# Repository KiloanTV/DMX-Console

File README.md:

<div>
  <h1 align="center">DMX Console</h1>

  <p align="center">
  <a href="https://blueprint.hackclub.com/">
    </img>
  </a>
  </p>
  <h1></h1>
  <p align="center">
    Nodes to build a custom DMX Console yourself!
  </p>
</div>

<sub align="center">This work is licensed under the
[MIT License](https://mit-license.org).
</sub>

## Table of Contents

- [About](#about)
- [Pictures](#pictures)
- [Bill of Materials](#bill-of-materials)

# About

I really wanted to build my own DMX Console but with modules and nodes so everyone can make a combination which work for themself. I havent designed the display driver board and the network switch yet but that will be in the V2 in the future.

# Pictures

# Bill of Materials

<details>
<summary><strong>Show Bill Of Materials(BOM) ----></strong></summary>

|Part Name                                     |Quantity                                    |Price            |Vendor    |Shipping Cost                                                  |Total Cost      |Link(if applicable)                                                                                                                                                                                                                                                                                                                                                                                                                                                                                                                                                                                                           |FIELD8|
|----------------------------------------------|--------------------------------------------|-----------------|----------|---------------------------------------------------------------|----------------|------------------------------------------------------------------------------------------------------------------------------------------------------------------------------------------------------------------------------------------------------------------------------------------------------------------------------------------------------------------------------------------------------------------------------------------------------------------------------------------------------------------------------------------------------------------------------------------------------------------------------|------|
|All 5 different PCBs + Stencils               |1x5 of each                                 |€84.74           |jlcpcb    |Shipping for all 3 PCB orders + taxes (see screenshot): €61.76 |                |                                                                                                                                                                                                                                                                                                                                                                                                                                                                                                                                                                                                                              |      |
|LCSC Electronic Components for 1x of every PCB|1 Order for everything(see lcsc cart export)|€135.83          |lcsc      |€49,63 (there is a Tariff for EU handling fees, see screenshot)|                |                                                                                                                                                                                                                                                                                                                                                                                                                                                                                                                                                                                                                              |      |
|motorized fader                               |4x1pcs                                      |€15,52           |alibaba   |€11.21                                                         |                |https://www.alibaba.com/product-detail/Terwin-X32-Motor-Fader-100mm-Travel_1601238129471.html?spm=a2700.prosearch.normal_offer.d_image.2e8f67afmJxxMf&priceId=ad31270e432b4abc9cdc3bcf5230f13c                                                                                                                                                                                                                                                                                                                                                                                                                                |      |
|Keyswitches                                   |4x1pcs                                      |€5,42            |aliexpress|€12.59                                                         |                |https://de.aliexpress.com/item/1005009946528694.html?spm=a2g0o.productlist.main.6.577b5ba0rvdL0e&algo_pvid=3587bc3c-6277-4f81-b946-1ec385545323&algo_exp_id=3587bc3c-6277-4f81-b946-1ec385545323-5&pdp_ext_f=%7B%22order%22%3A%2226%22%2C%22eval%22%3A%221%22%2C%22fromPage%22%3A%22search%22%7D&pdp_npi=6%40dis%21EUR%211.79%211.79%21%21%211.96%211.96%21%400b88ab8a17934589390817509e0f02%2112000050653018363%21sea%21DE%210%21X%211%210%21n_tag%3A-29919%3Bd%3A579054d5%3Bm03_new_user%3A-29895&curPageLogUid=jCaWmj7inoTK&utparam-url=scene%3Asearch%7Cquery_from%3A%7Cx_object_id%3A1005009946528694%7C_p_origin_prod%3A|      |
|Estimated Total                               |                                            |€241,51 ($270,48)|          |€135,19 ($151,41)                                              |€376,7 ($421,89)|                                                                                                                                                                                                                                                                                                                                                                                                                                                                                                                                                                                                                              |      |

</details>

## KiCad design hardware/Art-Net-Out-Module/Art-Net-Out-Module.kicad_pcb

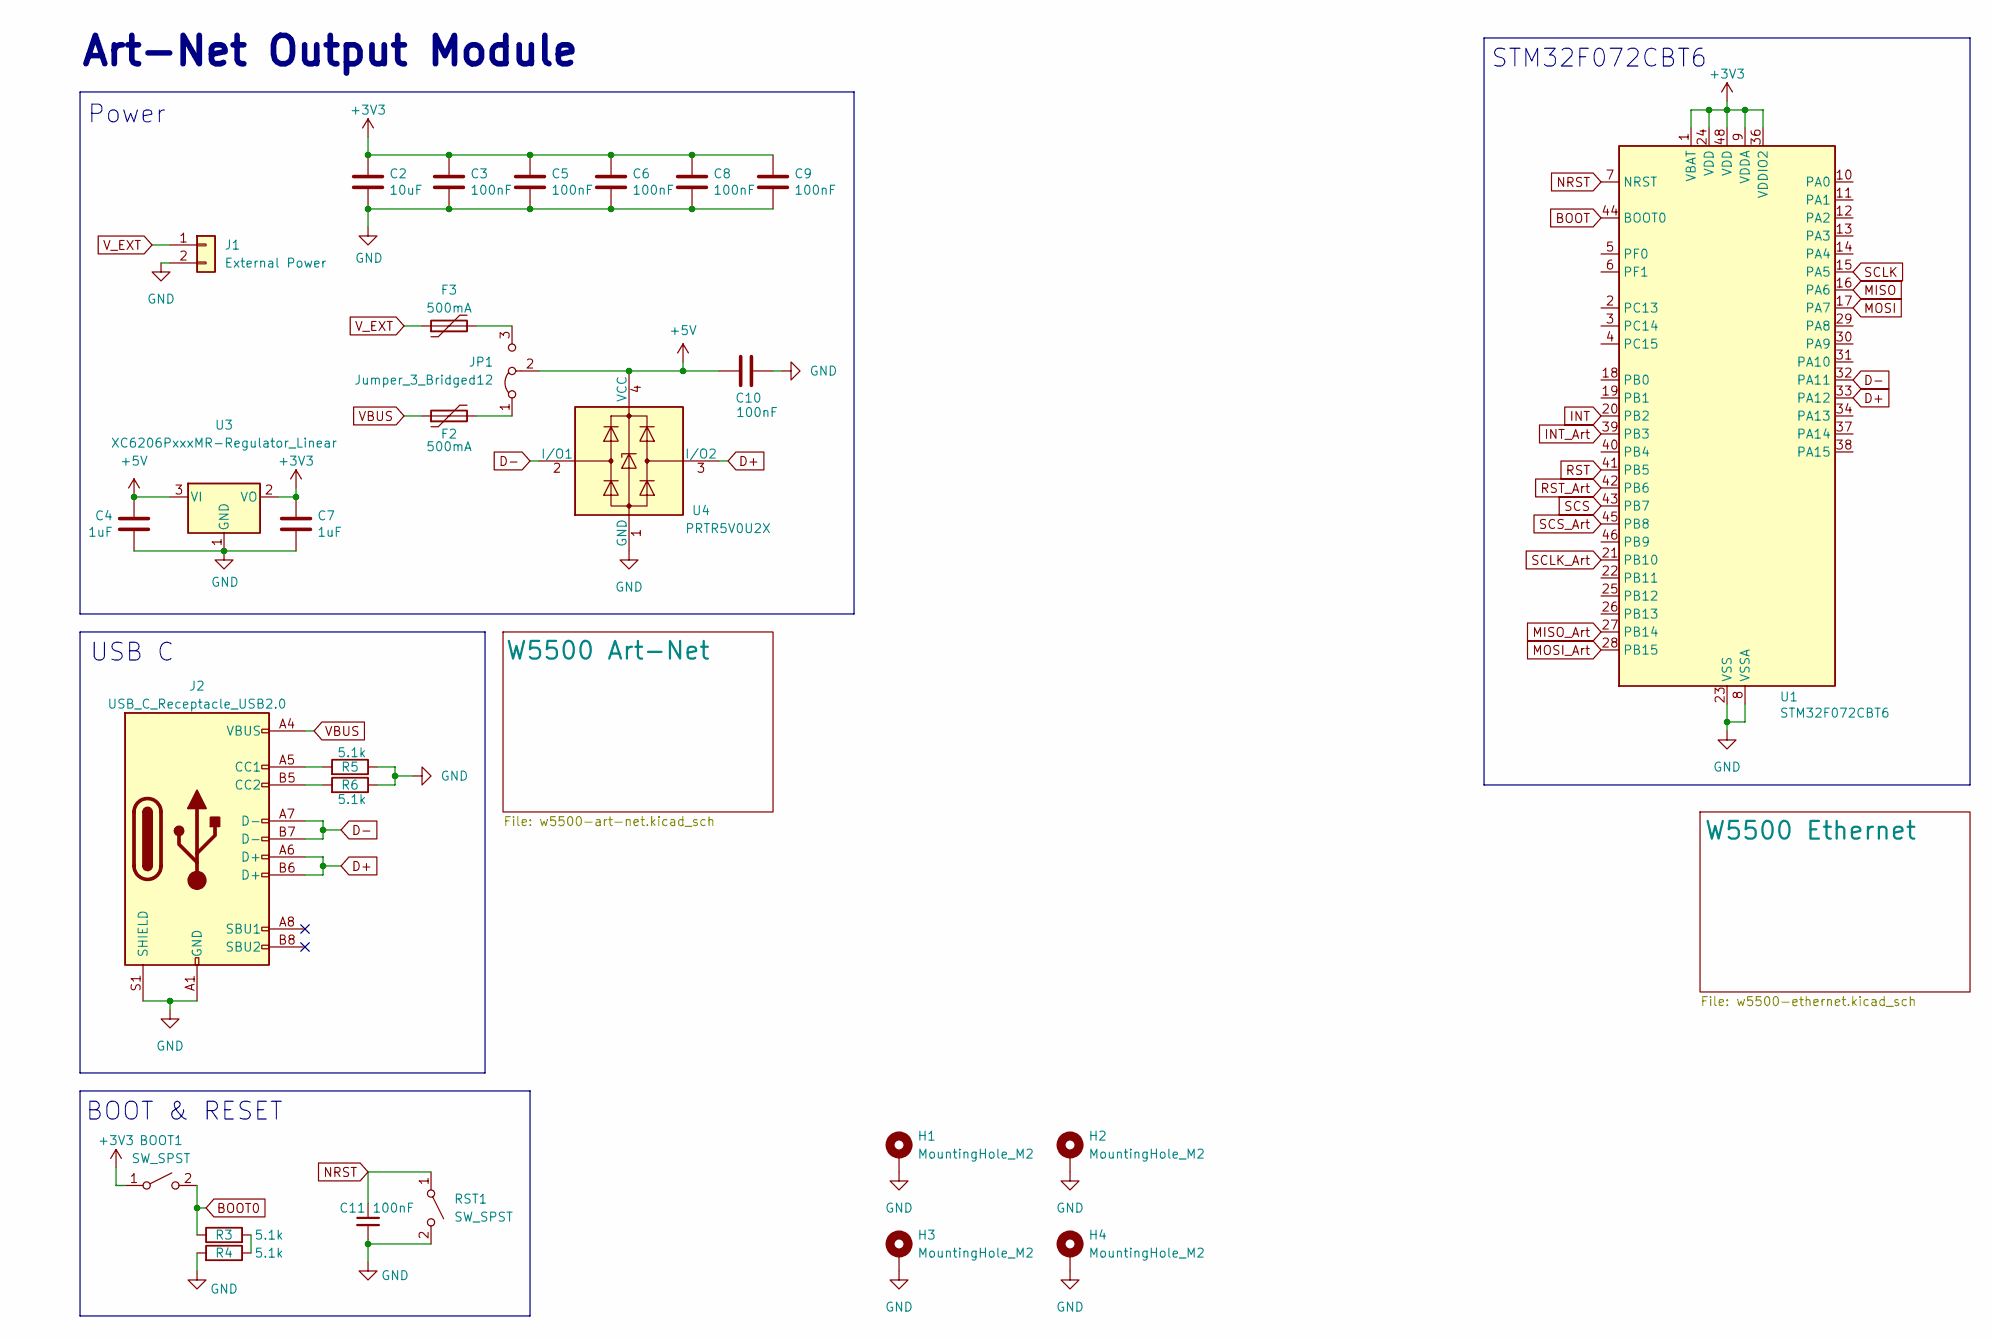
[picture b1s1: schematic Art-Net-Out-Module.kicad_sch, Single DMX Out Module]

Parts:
BOOT1: SW_SPST; SW_SPST_TL3342; LCSC C116647
C2: 10uF; C_0603_1608Metric; LCSC C19702
C3, C5, C6, C8, C9, C10, C11: 100nF; C_0402_1005Metric; LCSC C1525
C4, C7: 1uF; C_0402_1005Metric; LCSC C14445
F2, F3: 500mA; Fuse_1206_3216Metric; LCSC C135341
H1, H2, H3, H4: MountingHole_M2; MountingHole_2.2mm_M2_Pad_Via
J1: External Power; SolderWire-0.25sqmm_1x02_P4.5mm_D0.65mm_OD2mm
J2: USB_C_Receptacle_USB2.0; USB_C_HRO_TYPE-C-31-M-12; JlcRotOffset 180
JP1: Jumper_3_Bridged12; PinHeader_1x03_P2.54mm_Vertical; LCSC C42431836
R3, R4, R5, R6: 5.1k; R_0402_1005Metric; LCSC C105872
RST1: SW_SPST; SW_SPST_TL3342; LCSC C116647
U1: STM32F072CBT6; LQFP-48_7x7mm_P0.5mm; LCSC C81720
U3: XC6206PxxxMR-Regulator_Linear; SOT-23; LCSC C5446
U4: PRTR5V0U2X; SOT-143; LCSC C2827688

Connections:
+3V3: BOOT1.1 (A), C2.1, C3.1, C5.1, C6.1, C7.1, C8.1, C9.1, U1.1 (VBAT), U1.9 (VDDA), U1.24 (VDD), U1.36 (VDDIO2), U1.48 (VDD), U3.2 (VO); also elsewhere on the board
+5V: C4.1, C10.1, JP1.2 (C), U3.3 (VI), U4.4 (VCC)
D+: J2.A6 (D+), J2.B6 (D+), U1.33 (PA12), U4.3 (I/O2)
D-: J2.A7 (D-), J2.B7 (D-), U1.32 (PA11), U4.2 (I/O1)
GND: C2.2, C3.2, C4.2, C5.2, C6.2, C7.2, C8.2, C9.2, C10.2, C11.2, H1.1 (1_1), H2.1 (1_1), H3.1 (1_1), H4.1 (1_1), J1.2, J2.A1 (GND), J2.A12 (GND), J2.B1 (GND), J2.B12 (GND), J2.S1 (SHIELD), R4.2, R5.1, R6.1, RST1.2 (B), U1.8 (VSSA), U1.23 (VSS), U1.35 (VSS), U1.47 (VSS), U3.1 (GND), U4.1 (GND); also elsewhere on the board
INT: U1.20 (PB2); also elsewhere on the board
INT_Art: U1.39 (PB3); also elsewhere on the board
MISO: U1.16 (PA6); also elsewhere on the board
MISO_Art: U1.27 (PB14); also elsewhere on the board
MOSI: U1.17 (PA7); also elsewhere on the board
MOSI_Art: U1.28 (PB15); also elsewhere on the board
NRST: C11.1, RST1.1 (A), U1.7 (NRST)
unnamed: J2.A5 (CC1), R5.2
unnamed: J2.B5 (CC2), R6.2
unnamed: F2.2, JP1.1 (A)
unnamed: F3.2, JP1.3 (B)
unnamed: R3.2, R4.1
RST: U1.41 (PB5); also elsewhere on the board
RST_Art: U1.42 (PB6); also elsewhere on the board
SCLK: U1.15 (PA5); also elsewhere on the board
SCLK_Art: U1.21 (PB10); also elsewhere on the board
SCS: U1.43 (PB7); also elsewhere on the board
SCS_Art: U1.45 (PB8); also elsewhere on the board
VBUS: F2.1, J2.A4 (VBUS), J2.A9 (VBUS), J2.B4 (VBUS), J2.B9 (VBUS)
V_EXT: F3.1, J1.1

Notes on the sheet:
STM32F072CBT6
USB C
Power
Art-Net Output Module
BOOT & RESET

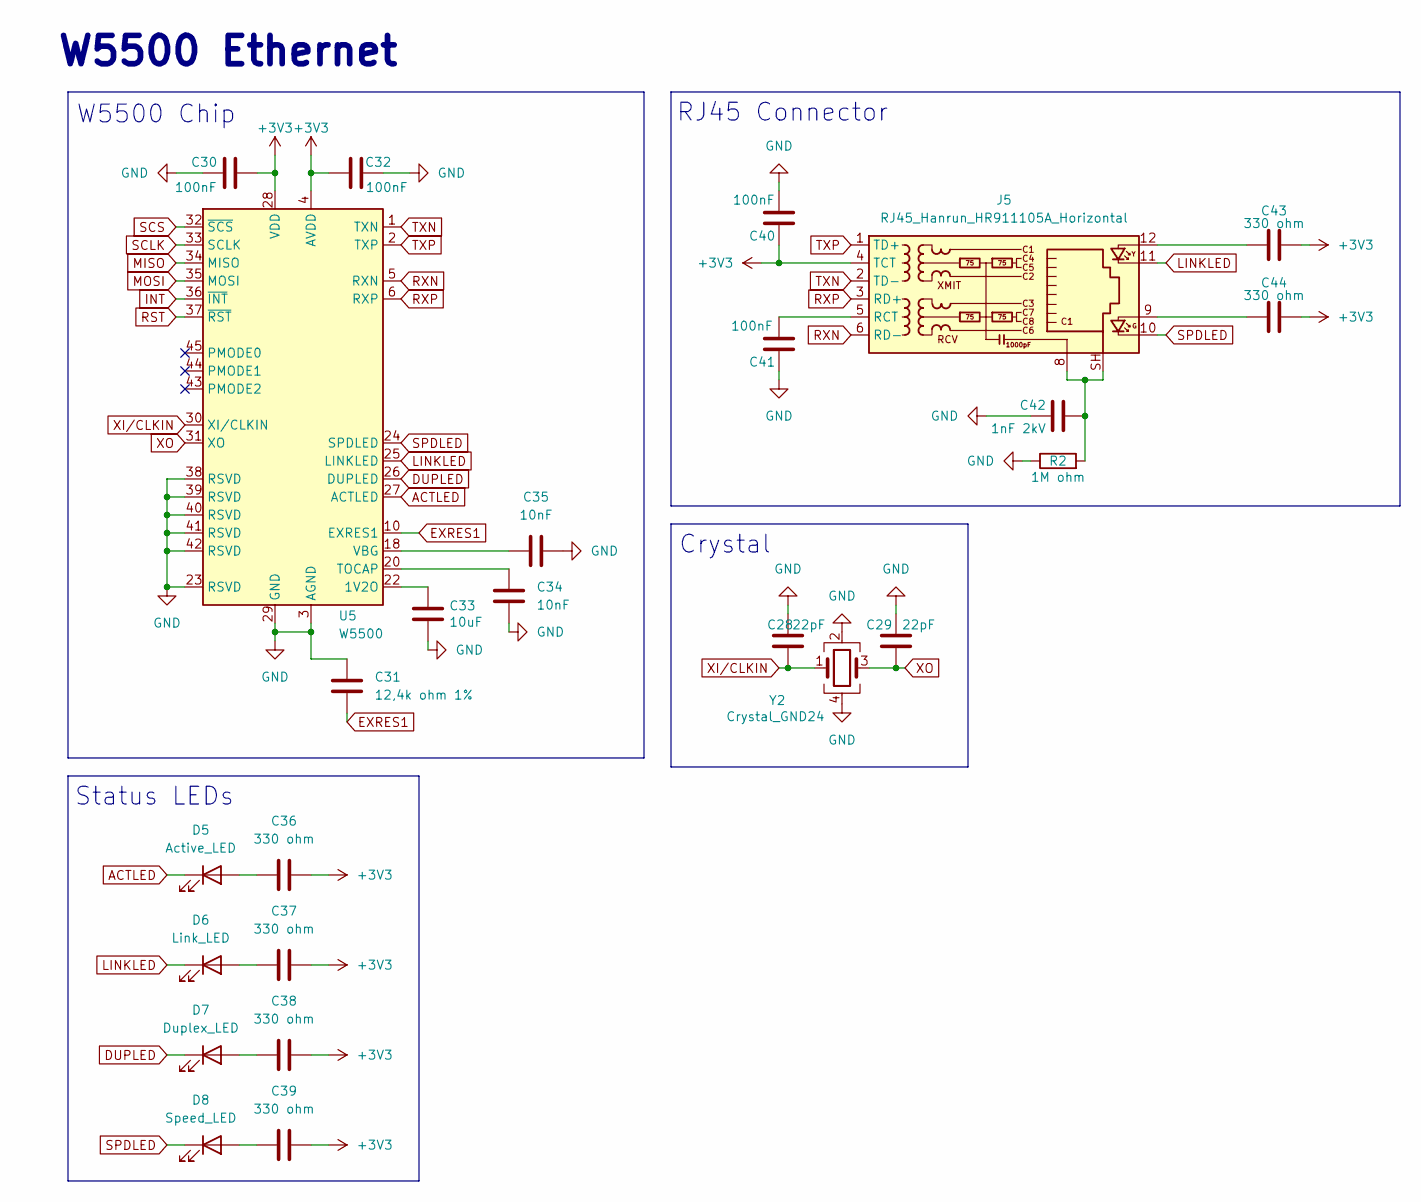
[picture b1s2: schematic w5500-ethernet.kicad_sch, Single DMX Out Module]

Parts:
C28, C29: 22pF; C_0603_1608Metric_Pad1.08x0.95mm_HandSolder; LCSC C1653
C30, C32, C40: 100nF; C_0402_1005Metric; LCSC C1525
C31: 12,4k ohm 1%; C_0603_1608Metric_Pad1.08x0.95mm_HandSolder; LCSC C2930060
C33: 10uF; C_0603_1608Metric; LCSC C19702
C34, C35: 10nF; C_0603_1608Metric_Pad1.08x0.95mm_HandSolder; LCSC C100042
C36, C37, C38, C39, C43, C44: 330 ohm; C_0603_1608Metric_Pad1.08x0.95mm_HandSolder; LCSC C105881
C41: 100nF; C_0402_1005Metric; LCSC C49056139
C42: 1nF 2kV; C_1206_3216Metric_Pad1.33x1.80mm_HandSolder; LCSC C23631
D5: Active_LED; LED_0603_1608Metric_Pad1.05x0.95mm_HandSolder; LCSC C19273151
D6: Link_LED; LED_0603_1608Metric_Pad1.05x0.95mm_HandSolder; LCSC C19171392
D7: Duplex_LED; LED_0603_1608Metric_Pad1.05x0.95mm_HandSolder; LCSC C19273150
D8: Speed_LED; LED_0603_1608Metric_Pad1.05x0.95mm_HandSolder; LCSC C19273152
J5: RJ45_Hanrun_HR911105A_Horizontal; LCSC C12074
R2: 1M ohm; R_1206_3216Metric_Pad1.30x1.75mm_HandSolder; LCSC C46961738
U5: W5500; LQFP-48_7x7mm_P0.5mm
Y2: Crystal_GND24; Crystal_SMD_3225-4Pin_3.2x2.5mm_HandSoldering; LCSC C9006

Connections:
+3V3: C30.1, C32.1, C36.2, C37.2, C38.2, C39.2, C40.2, C43.2, C44.2, J5.4 (TCT), U5.4 (AVDD), U5.8 (AVDD), U5.11 (AVDD), U5.15 (AVDD), U5.17 (AVDD), U5.21 (AVDD), U5.28 (VDD); also elsewhere on the board
ACTLED: D5.1 (K), U5.27 (ACTLED)
DUPLED: D7.1 (K), U5.26 (DUPLED)
EXRES1: C31.2, U5.10 (EXRES1)
GND: C28.1, C29.1, C30.2, C31.1, C32.2, C33.2, C34.2, C35.2, C40.1, C41.2, C42.1, R2.1, U5.3 (AGND), U5.9 (AGND), U5.14 (AGND), U5.16 (AGND), U5.19 (AGND), U5.23 (RSVD), U5.29 (GND), U5.38 (RSVD), U5.39 (RSVD), U5.40 (RSVD), U5.41 (RSVD), U5.42 (RSVD), U5.48 (AGND), Y2.2, Y2.4; also elsewhere on the board
INT: U5.36 (~INT); also elsewhere on the board
LINKLED: D6.1 (K), J5.11, U5.25 (LINKLED)
MISO: U5.34 (MISO); also elsewhere on the board
MOSI: U5.35 (MOSI); also elsewhere on the board
unnamed: C42.2, J5.8, J5.SH, R2.2
unnamed: C43.1, J5.12
unnamed: C44.1, J5.9
unnamed: C36.1, D5.2 (A)
unnamed: C37.1, D6.2 (A)
unnamed: C38.1, D7.2 (A)
unnamed: C39.1, D8.2 (A)
unnamed: C41.1, J5.5 (RCT)
unnamed: C33.1, U5.22 (1V2O)
unnamed: C34.1, U5.20 (TOCAP)
unnamed: C35.1, U5.18 (VBG)
RST: U5.37 (~RST); also elsewhere on the board
RXN: J5.6 (RD-), U5.5 (RXN)
RXP: J5.3 (RD+), U5.6 (RXP)
SCLK: U5.33 (SCLK); also elsewhere on the board
SCS: U5.32 (~SCS); also elsewhere on the board
SPDLED: D8.1 (K), J5.10, U5.24 (SPDLED)
TXN: J5.2 (TD-), U5.1 (TXN)
TXP: J5.1 (TD+), U5.2 (TXP)
XI/CLKIN: C28.2, U5.30 (XI/CLKIN), Y2.1
XO: C29.2, U5.31 (XO), Y2.3

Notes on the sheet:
RJ45 Connector
W5500 Ethernet
Crystal
W5500 Chip
Status LEDs

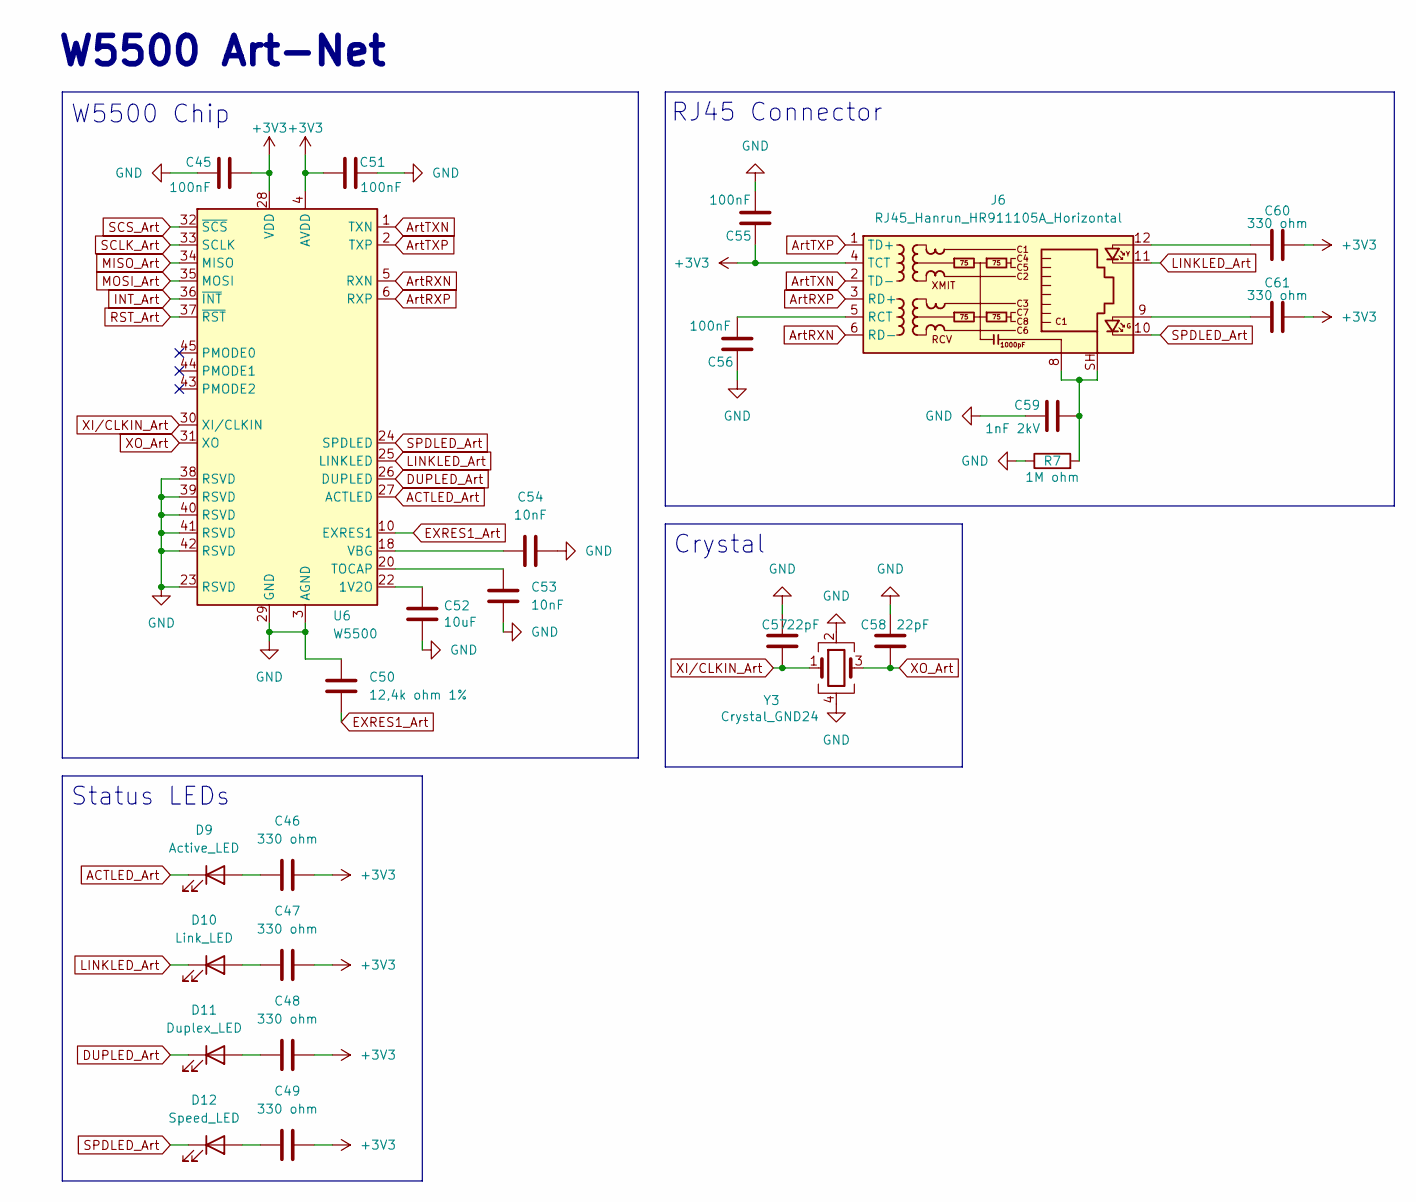
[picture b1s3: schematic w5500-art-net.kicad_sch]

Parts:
C45, C51, C55: 100nF; C_0402_1005Metric; LCSC C1525
C46, C47, C48, C49, C60, C61: 330 ohm; C_0603_1608Metric_Pad1.08x0.95mm_HandSolder; LCSC C105881
C50: 12,4k ohm 1%; C_0603_1608Metric_Pad1.08x0.95mm_HandSolder; LCSC C2930060
C52: 10uF; C_0603_1608Metric; LCSC C19702
C53, C54: 10nF; C_0603_1608Metric_Pad1.08x0.95mm_HandSolder; LCSC C100042
C56: 100nF; C_0402_1005Metric; LCSC C49056139
C57, C58: 22pF; C_0603_1608Metric_Pad1.08x0.95mm_HandSolder; LCSC C1653
C59: 1nF 2kV; C_1206_3216Metric_Pad1.33x1.80mm_HandSolder; LCSC C23631
D9: Active_LED; LED_0603_1608Metric_Pad1.05x0.95mm_HandSolder; LCSC C19273151
D10: Link_LED; LED_0603_1608Metric_Pad1.05x0.95mm_HandSolder; LCSC C19171392
D11: Duplex_LED; LED_0603_1608Metric_Pad1.05x0.95mm_HandSolder; LCSC C19273150
D12: Speed_LED; LED_0603_1608Metric_Pad1.05x0.95mm_HandSolder; LCSC C19273152
J6: RJ45_Hanrun_HR911105A_Horizontal; LCSC C12074
R7: 1M ohm; R_1206_3216Metric_Pad1.30x1.75mm_HandSolder; LCSC C46961738
U6: W5500; LQFP-48_7x7mm_P0.5mm
Y3: Crystal_GND24; Crystal_SMD_3225-4Pin_3.2x2.5mm_HandSoldering; LCSC C9006

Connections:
+3V3: C45.1, C46.2, C47.2, C48.2, C49.2, C51.1, C55.2, C60.2, C61.2, J6.4 (TCT), U6.4 (AVDD), U6.8 (AVDD), U6.11 (AVDD), U6.15 (AVDD), U6.17 (AVDD), U6.21 (AVDD), U6.28 (VDD); also elsewhere on the board
ACTLED_Art: D9.1 (K), U6.27 (ACTLED)
ArtRXN: J6.6 (RD-), U6.5 (RXN)
ArtRXP: J6.3 (RD+), U6.6 (RXP)
ArtTXN: J6.2 (TD-), U6.1 (TXN)
ArtTXP: J6.1 (TD+), U6.2 (TXP)
DUPLED_Art: D11.1 (K), U6.26 (DUPLED)
EXRES1_Art: C50.2, U6.10 (EXRES1)
GND: C45.2, C50.1, C51.2, C52.2, C53.2, C54.2, C55.1, C56.2, C57.1, C58.1, C59.1, R7.1, U6.3 (AGND), U6.9 (AGND), U6.14 (AGND), U6.16 (AGND), U6.19 (AGND), U6.23 (RSVD), U6.29 (GND), U6.38 (RSVD), U6.39 (RSVD), U6.40 (RSVD), U6.41 (RSVD), U6.42 (RSVD), U6.48 (AGND), Y3.2, Y3.4; also elsewhere on the board
INT_Art: U6.36 (~INT); also elsewhere on the board
LINKLED_Art: D10.1 (K), J6.11, U6.25 (LINKLED)
MISO_Art: U6.34 (MISO); also elsewhere on the board
MOSI_Art: U6.35 (MOSI); also elsewhere on the board
unnamed: C59.2, J6.8, J6.SH, R7.2
unnamed: C60.1, J6.12
unnamed: C61.1, J6.9
unnamed: C46.1, D9.2 (A)
unnamed: C47.1, D10.2 (A)
unnamed: C48.1, D11.2 (A)
unnamed: C49.1, D12.2 (A)
unnamed: C56.1, J6.5 (RCT)
unnamed: C52.1, U6.22 (1V2O)
unnamed: C53.1, U6.20 (TOCAP)
unnamed: C54.1, U6.18 (VBG)
RST_Art: U6.37 (~RST); also elsewhere on the board
SCLK_Art: U6.33 (SCLK); also elsewhere on the board
SCS_Art: U6.32 (~SCS); also elsewhere on the board
SPDLED_Art: D12.1 (K), J6.10, U6.24 (SPDLED)
XI/CLKIN_Art: C57.2, U6.30 (XI/CLKIN), Y3.1
XO_Art: C58.2, U6.31 (XO), Y3.3

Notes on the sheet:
W5500 Chip
RJ45 Connector
Crystal
Status LEDs
W5500 Art-Net

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
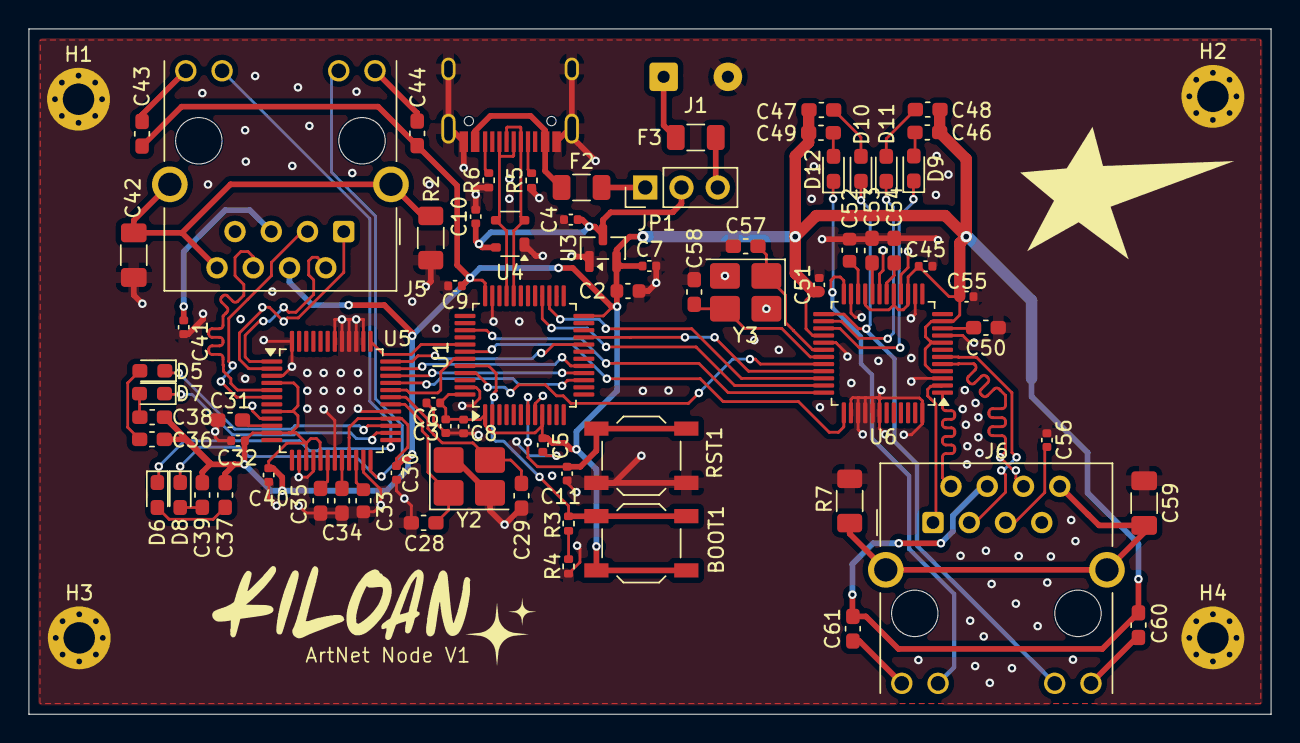
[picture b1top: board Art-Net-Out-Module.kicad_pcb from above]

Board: 2 copper layers, 87.0 x 48.0 mm, 78 parts (0 on the bottom side), 70 nets.

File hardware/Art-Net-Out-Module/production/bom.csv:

Designator,Footprint,Quantity,Value,LCSC Part #
"BOOT1, RST1",SW_SPST_TL3342,2,SW_SPST,C116647
"C10, C11, C3, C30, C32, C40, C45, C5, C51, C55, C6, C8, C9",0402,13,100nF,C1525
"C2, C33, C52",0603,3,10uF,C19702
"C28, C29, C57, C58",0603,4,22pF,C1653
"C31, C50",0603,2,"12,4k ohm 1%",C2930060
"C34, C35, C53, C54",0603,4,10nF,C100042
"C36, C37, C38, C39, C43, C44, C46, C47, C48, C49, C60, C61",0603,12,330 ohm,C105881
"C4, C7",0402,2,1uF,C14445
"C41, C56",0402,2,100nF,C49056139
"C42, C59",1206,2,1nF 2kV,C23631
"D10, D6",0603,2,Link_LED,C19171392
"D11, D7",0603,2,Duplex_LED,C19273150
"D12, D8",0603,2,Speed_LED,C19273152
"D5, D9",0603,2,Active_LED,C19273151
"F2, F3",1206,2,500mA,C135341
J1,SolderWire-0.25sqmm_1x02_P4.5mm_D0.65mm_OD2mm,1,External Power,
J2,USB_C_HRO_TYPE-C-31-M-12,1,USB_C_Receptacle_USB2.0,C165948
"J5, J6",RJ45_Hanrun_HR911105A_Horizontal,2,RJ45_Hanrun_HR911105A_Horizontal,C12074
"R2, R7",1206,2,1M ohm,C46961738
"R3, R4, R5, R6",0402,4,5.1k,C105872
U1,LQFP-48_7x7mm_P0.5mm,1,STM32F072CBT6,C81720
U3,SOT-23,1,XC6206PxxxMR-Regulator_Linear,C5446
U4,SOT-143,1,PRTR5V0U2X,C2827688
"U5, U6",LQFP-48_7x7mm_P0.5mm,2,W5500,
"Y2, Y3",Crystal_SMD_3225-4Pin_3.2x2.5mm_HandSoldering,2,Crystal_GND24,C9006

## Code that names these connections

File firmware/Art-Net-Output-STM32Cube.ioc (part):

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Mcu.Name=STM32F072C(8-B)Tx
Mcu.Package=LQFP48
Mcu.UserName=STM32F072CBTx
PA11.Mode=Device
PA11.Signal=USB_DM
PA12.Mode=Device
PA12.Signal=USB_DP
PA5.Mode=Full_Duplex_Master
PA5.Signal=SPI1_SCK
PA6.Mode=Full_Duplex_Master
PA6.Signal=SPI1_MISO
PA7.Mode=Full_Duplex_Master
PA7.Signal=SPI1_MOSI
PB10.Mode=Full_Duplex_Master
PB10.Signal=SPI2_SCK
PB14.Mode=Full_Duplex_Master
PB14.Signal=SPI2_MISO
PB15.Mode=Full_Duplex_Master
PB15.Signal=SPI2_MOSI
PB2.GPIOParameters=GPIO_PuPd,GPIO_Label,GPIO_ModeDefaultEXTI
PB2.GPIO_Label=INT_ethernet
PB2.GPIO_ModeDefaultEXTI=GPIO_MODE_IT_FALLING
PB2.GPIO_PuPd=GPIO_PULLUP
PB2.Signal=GPXTI2
PB3.GPIOParameters=GPIO_PuPd,GPIO_Label,GPIO_ModeDefaultEXTI
PB3.GPIO_Label=INT-artnet
PB3.GPIO_ModeDefaultEXTI=GPIO_MODE_IT_FALLING
PB3.GPIO_PuPd=GPIO_PULLUP
PB3.Signal=GPXTI3
PB5.GPIOParameters=GPIO_PuPd,GPIO_Label
PB5.GPIO_Label=RST_ethernet
PB5.GPIO_PuPd=GPIO_PULLUP
PB5.Signal=GPIO_Output
PB6.GPIOParameters=GPIO_PuPd,GPIO_Label
PB6.GPIO_Label=RST_artnet
PB6.GPIO_PuPd=GPIO_PULLUP
PB6.Signal=GPIO_Output
PB7.GPIOParameters=GPIO_PuPd,GPIO_Label
PB7.GPIO_Label=SCS_ethernet
PB7.GPIO_PuPd=GPIO_PULLUP
PB7.Signal=GPIO_Output
PB8.GPIOParameters=GPIO_PuPd,GPIO_Label
PB8.GPIO_Label=SCS_artnet
PB8.GPIO_PuPd=GPIO_PULLUP
PB8.Signal=GPIO_Output
board=custom
